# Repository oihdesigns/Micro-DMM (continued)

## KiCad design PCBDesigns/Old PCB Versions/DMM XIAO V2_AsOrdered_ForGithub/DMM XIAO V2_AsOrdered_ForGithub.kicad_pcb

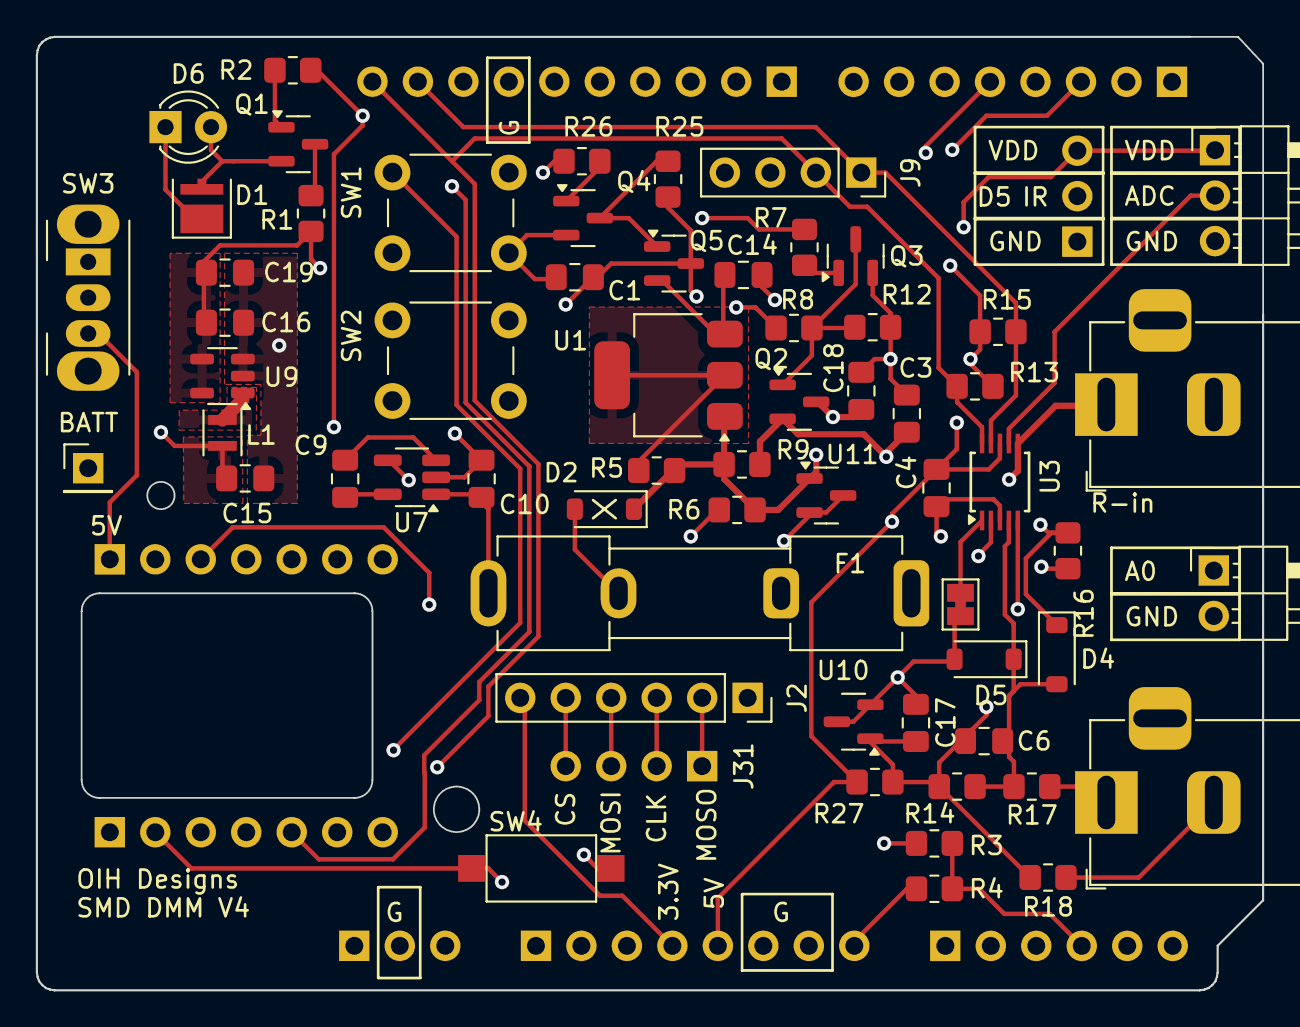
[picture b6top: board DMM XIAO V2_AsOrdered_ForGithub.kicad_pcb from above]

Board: 4 copper layers, 68.5 x 53.2 mm, 70 parts (0 on the bottom side), 45 nets.

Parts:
C1: 0.47uF; C_0805_2012Metric_Pad1.18x1.45mm_HandSolder
C3, C14: 2.2uF; C_0805_2012Metric_Pad1.18x1.45mm_HandSolder
C4, C17: 0.1uF; C_0805_2012Metric_Pad1.18x1.45mm_HandSolder
C6: ? DNP; C_0805_2012Metric_Pad1.18x1.45mm_HandSolder
C9, C10, C15: 4.7uF; C_0805_2012Metric_Pad1.18x1.45mm_HandSolder
C16, C19: 22uF; C_0805_2012Metric_Pad1.18x1.45mm_HandSolder
C18: 1uF; C_0805_2012Metric_Pad1.18x1.45mm_HandSolder
D1: LED; LED_Luminus_MP-3030-1100_3.0x3.0mm
D2: R Circuit V Clamp; D_SOD-123
D4, D5: D_Schottky; D_SOD-123
D6: LED; LED_D3.0mm_Clear
F1: Fuse; Fuseholder_Clip-5x20mm_Keystone_3512P_Inline_P23.62x7.27mm_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
J1, J3: Conn_01x07_Pin; PinSocket_1x07_P2.54mm_Vertical
J2: MicoSD; PinSocket_1x06_P2.54mm_Vertical
J4: IR Connection; PinHeader_1x03_P2.54mm_Vertical_NoBox
J5: POWER2; PinHeader_1x03_P2.54mm_Vertical_NoBox
J6: POWER1; PinHeader_1x08_P2.54mm_Vertical_NoBox
J8: DIGITAL2; PinHeader_1x10_P2.54mm_Vertical_NoBox
J9: Out to Screen; PinSocket_1x04_P2.54mm_Vertical
J10: ANALOG; PinHeader_1x06_P2.54mm_Vertical_NoBox
J11: I_Input; PinHeader_1x03_P2.54mm_Horizontal
J12: Conn_01x02_Pin; PinHeader_1x02_P2.54mm_Horizontal
J13: DIGITAL1; PinHeader_1x08_P2.54mm_Vertical_NoBox
J14, J15: Barrel_Jack; BarrelJack_Horizontal
J31: Conn_01x04; PinHeader_1x04_P2.54mm_Vertical
JP6: Jumper_2_Bridged; SolderJumper-2_P1.3mm_Bridged_Pad1.0x1.5mm
L1: 2.2uH; L_Murata_DFE201610P
Q1, Q3, Q4, Q5: MMBT3904; SOT-23
Q2: SI2302 MOSFET; SOT-23
R1: 500; R_0805_2012Metric_Pad1.20x1.40mm_HandSolder
R2, R13, R15, R16, R25, R26: 1K; R_0805_2012Metric_Pad1.20x1.40mm_HandSolder
R3, R7, R8: 22K; R_0805_2012Metric_Pad1.20x1.40mm_HandSolder
R4: 100K; R_0805_2012Metric_Pad1.20x1.40mm_HandSolder
R5: 62.0; R_0805_2012Metric_Pad1.20x1.40mm_HandSolder
R6: 330.0; R_0805_2012Metric_Pad1.20x1.40mm_HandSolder
R9, R14: 22.0K; R_0805_2012Metric_Pad1.20x1.40mm_HandSolder
R12, R27: 4.7K; R_0805_2012Metric_Pad1.20x1.40mm_HandSolder
R17, R18: 500.0K; R_0805_2012Metric_Pad1.20x1.40mm_HandSolder
SW1, SW2: SW_Push; SW_PUSH_6mm
SW3: SW_SPDT; SW_Slide_SPDT_Angled_CK_OS102011MA1Q
SW4: SW_Push; SW_SPST_CK_RS282G05A3
TP3: Batt Input; PinHeader_1x01_P2.54mm_Vertical
U1: LM317_TO-220; SOT-223-3_TabPin2
U3: ADS1115IDGS; TSSOP-10_3x3mm_P0.5mm
U7: MAX1683; SOT-23-5_HandSoldering
U9: TPS613222ADBV; SOT-23-5
U10: LM4040DBZ-2.5; SOT-23
U11: LM4040DBZ-5; SOT-23

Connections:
+3V3: J1.3, J2.6, J6.4
+9V: C1.1, C10.2, Q5.3 (C), R8.1, R25.2, U7.2 (Out)
+BATT: J6.8, R4.2, SW3.1 (A), TP3.1
/R Circuit I Output: C18.1, D2.1 (K), Q2.3 (D), R5.2, R6.2, R9.1, U1.1 (ADJ), U11.1 (K)
/V Ref to ADS: C6.1, C17.2, R14.1, R18.2, R27.2, U3.5 (AIN1), U10.1 (K)
/V Signal to ADS: C6.2, D4.2 (A), D5.1 (K), R14.2, R17.2, U3.4 (AIN0)
A0/D14: J3.1, J10.1, J12.1
A1/D15: J3.2, J10.2, SW4.1
A2/D16: J3.3, J10.3
A3/D17: J10.4, R3.2, R4.1
ADS_ADDR: JP6.2 (B), U3.1 (ADDR)
ADS_ALERT: R16.1, U3.2 (ALERT/RDY)
CLK: J2.3, J31.2
CS: J2.5, J31.4
D3~: J3.4, J13.4, SW1.1
D5~ (IR): J1.6, J4.2, J13.6
D6~: J3.7, J13.7, R2.1
D7: J1.7, J13.8, R7.1
D9~: J1.5, J13.3, R26.2
D10~: J1.4, J13.5, SW2.1
GND: C1.2, C3.2, C4.1, C10.1, C14.2, C15.2, C16.2, C17.1, C18.2, C19.2, D1.1 (K), D2.2 (A), D5.2 (A), D6.1 (K), F1.2, J1.2, J2.1, J4.1, J5.2, J6.6, J6.7, J8.7, J9.4, J11.3, J12.2, JP6.1 (A), Q3.2 (E), Q4.2 (E), R3.1, R6.1, R12.1, SW1.2, SW2.2, SW4.2, U3.3 (GND), U7.1 (Gnd), U9.2 (GND), U10.2 (A), U10.3 (nc_(gnd)), U11.2 (A), U11.3 (nc_(gnd))
I_Input: J11.2, U3.7 (AIN3)
MISO: J2.2, J31.1
MOSI: J2.4, J31.3
unnamed: D1.2 (A), D6.2 (A), Q1.2 (E)
unnamed: F1.1, J14.2
unnamed: Q1.1 (B), R2.2
unnamed: Q1.3 (C), R1.1
unnamed: Q2.1 (G), Q3.3 (C), R8.2, R12.2
unnamed: Q3.1 (B), R7.2
unnamed: Q4.1 (B), R26.1
unnamed: Q4.3 (C), Q5.1 (B), R25.1
unnamed: C14.1, Q5.2 (E), U1.3 (VI)
unnamed: R5.1, U1.2 (VO)
unnamed: C9.2, U7.5 (C1+)
unnamed: C9.1, U7.3 (C1-)
unnamed: L1.2, U9.1 (SW), U9.3 (nc_(gnd))
Resistor_Input: C3.1, J14.1, Q2.2 (S), R9.2, U3.6 (AIN2)
SCL: J3.6, J8.10, J9.2, R13.1, U3.10 (SCL)
SDA: J3.5, J8.9, J9.1, R15.1, U3.9 (SDA)
VDD: C4.2, C16.1, C19.1, D4.1 (K), J4.3, J6.5, J9.3, J11.1, R1.2, R13.2, R15.2, R16.2, R27.1, U3.8 (VDD), U7.4 (In), U9.4 (VOUT), U9.5 (nc_(vdd))
V_Input_Float: J15.1, R17.1
V_Input_REF: J15.2, R18.1
XIAO 5V: J1.1, SW3.3 (C)
XIAO Batt Pin: C15.1, L1.1, SW3.2 (B)

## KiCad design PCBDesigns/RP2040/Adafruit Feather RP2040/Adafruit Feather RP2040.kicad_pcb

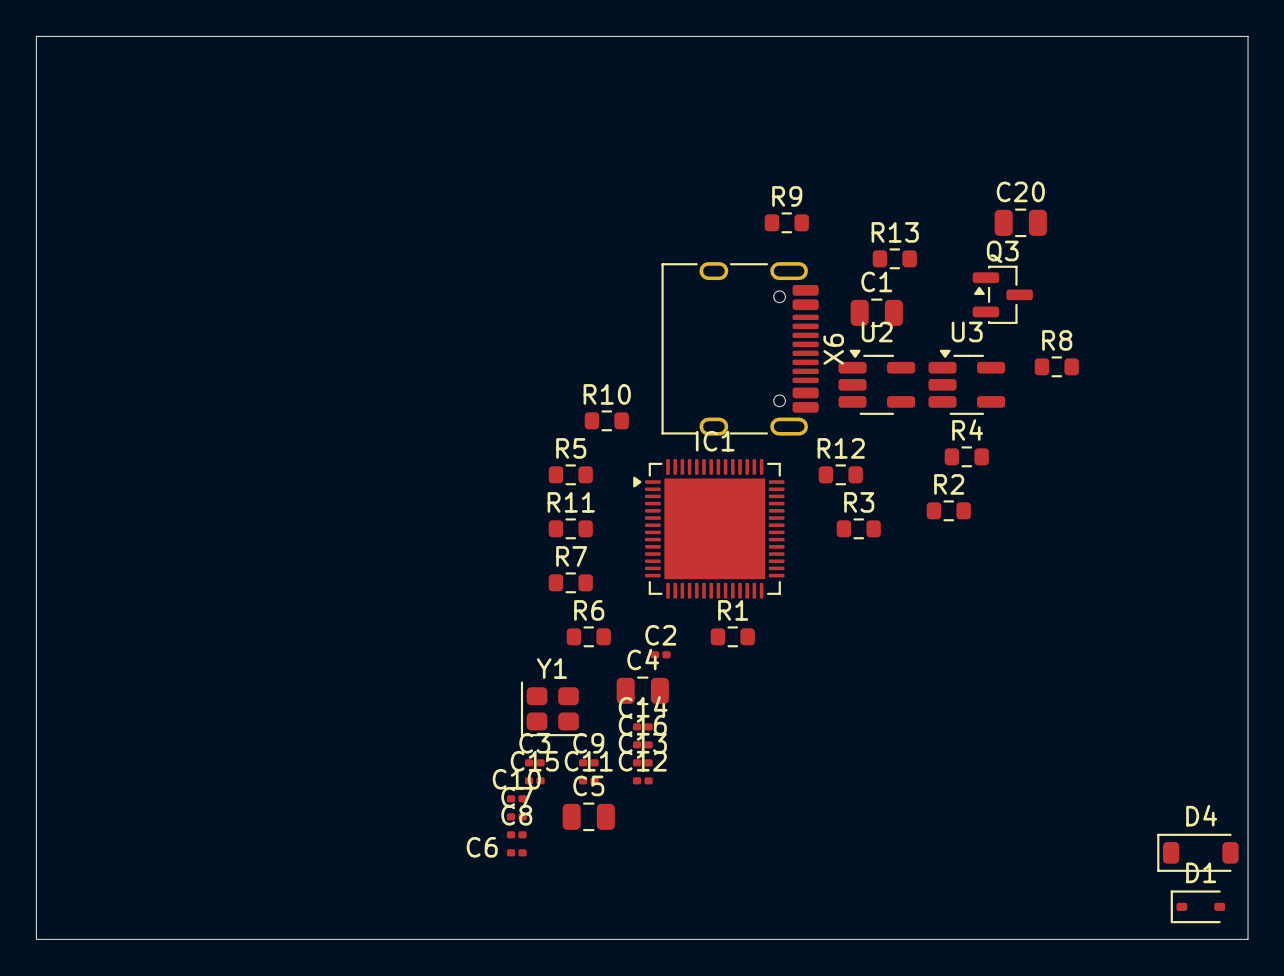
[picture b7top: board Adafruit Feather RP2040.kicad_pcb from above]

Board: 2 copper layers, 67.3 x 50.2 mm, 38 parts (0 on the bottom side), 21 nets, no tracks yet.

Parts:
C1, C4, C5, C20: 10uF; C_0805_2012Metric
C2, C3: 22pF; C_0201_0603Metric
C6, C7, C9, C11, C12, C13, C14, C15, C16: 0.1uF; C_0201_0603Metric
C8, C10: 1uF; C_0201_0603Metric
D1: NSR0320; D_SOD-323
D4: MBR0540; D_SOD-123
IC1: RP2040_QFN56; QFN-56-1EP_7x7mm_P0.4mm_EP5.6x5.6mm
Q3: DMG3415; SOT-23
R1, R2, R3, R4, R5, R7: 10K; R_0603_1608Metric
R6, R11: 1K; R_0603_1608Metric
R8, R12, R13: 5.1K; R_0603_1608Metric
R9, R10: 27; R_0603_1608Metric
U2: RT9080/AP2112-3.3; SOT-23-5_HandSoldering
U3: MCP73831T-2ACI/OT; SOT-23-5_HandSoldering
X6: USB Type C; USB_C_Receptacle_HRO_TYPE-C-31-M-12
Y1: 12MHz/12pF; Crystal_SMD_2520-4Pin_2.5x2.0mm

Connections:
1.2V: C6.2, C7.2, C8.1, IC1.23 (DVDD), IC1.45 (VREG_VOUT), IC1.50 (DVDD)
+3V3: C4.1, C5.1, C9.1, C10.1, C11.1, C12.1, C13.1, C14.1, C15.1, C16.1, IC1.1 (IOVDD), IC1.10 (IOVDD), IC1.22 (IOVDD), IC1.33 (IOVDD), IC1.42 (IOVDD), IC1.43 (ADC_IOVDD), IC1.44 (VREG_IOVDD), IC1.48 (USB_IOVDD), IC1.49 (IOVDD), R1.1, R5.2, U2.5 (OUT)
/CC1: R13.2, X6.A5 (CC1)
/CC2: R12.2, X6.B5 (CC2)
/D13: IC1.16 (GPIO13), R7.1
/D+: IC1.47 (USB_D+), R10.2
/D-: IC1.46 (USB_D-), R9.2
/EN: R3.1, U2.3 (EN)
/QSPI_CS: IC1.56 (~QSPI_CS), R5.1, R11.1
/USB_D+: R10.1, X6.A6 (D+), X6.B6 (D+)
/USB_D-: R9.1, X6.A7 (D-), X6.B7 (D-)
/VHI: C1.1, Q3.2 (S), R3.2, U2.1 (IN)
/~RESET: IC1.26 (/RUN), R1.2
GND: C1.2, C2.1, C3.1, C4.2, C5.2, C6.1, C7.1, C8.2, C9.2, C10.2, C11.2, C12.2, C13.2, C14.2, C15.2, C16.2, C20.2, IC1.19 (TESTEN), R4.1, R8.2, R12.1, R13.1, U2.2 (GND), U3.2 (VSS)
unnamed: C3.2, R6.1, Y1.1
unnamed: C2.2, IC1.20 (XIN), Y1.3 (2)
unnamed: IC1.21 (XOUT), R6.2
unnamed: R8.1, U3.5 (PROG)
unnamed: R2.2, U3.1 (STAT)
VBAT: C20.1, Q3.3 (D), U3.3 (VBAT)
VBUS: Q3.1 (G), R4.2, U3.4 (VDD)
